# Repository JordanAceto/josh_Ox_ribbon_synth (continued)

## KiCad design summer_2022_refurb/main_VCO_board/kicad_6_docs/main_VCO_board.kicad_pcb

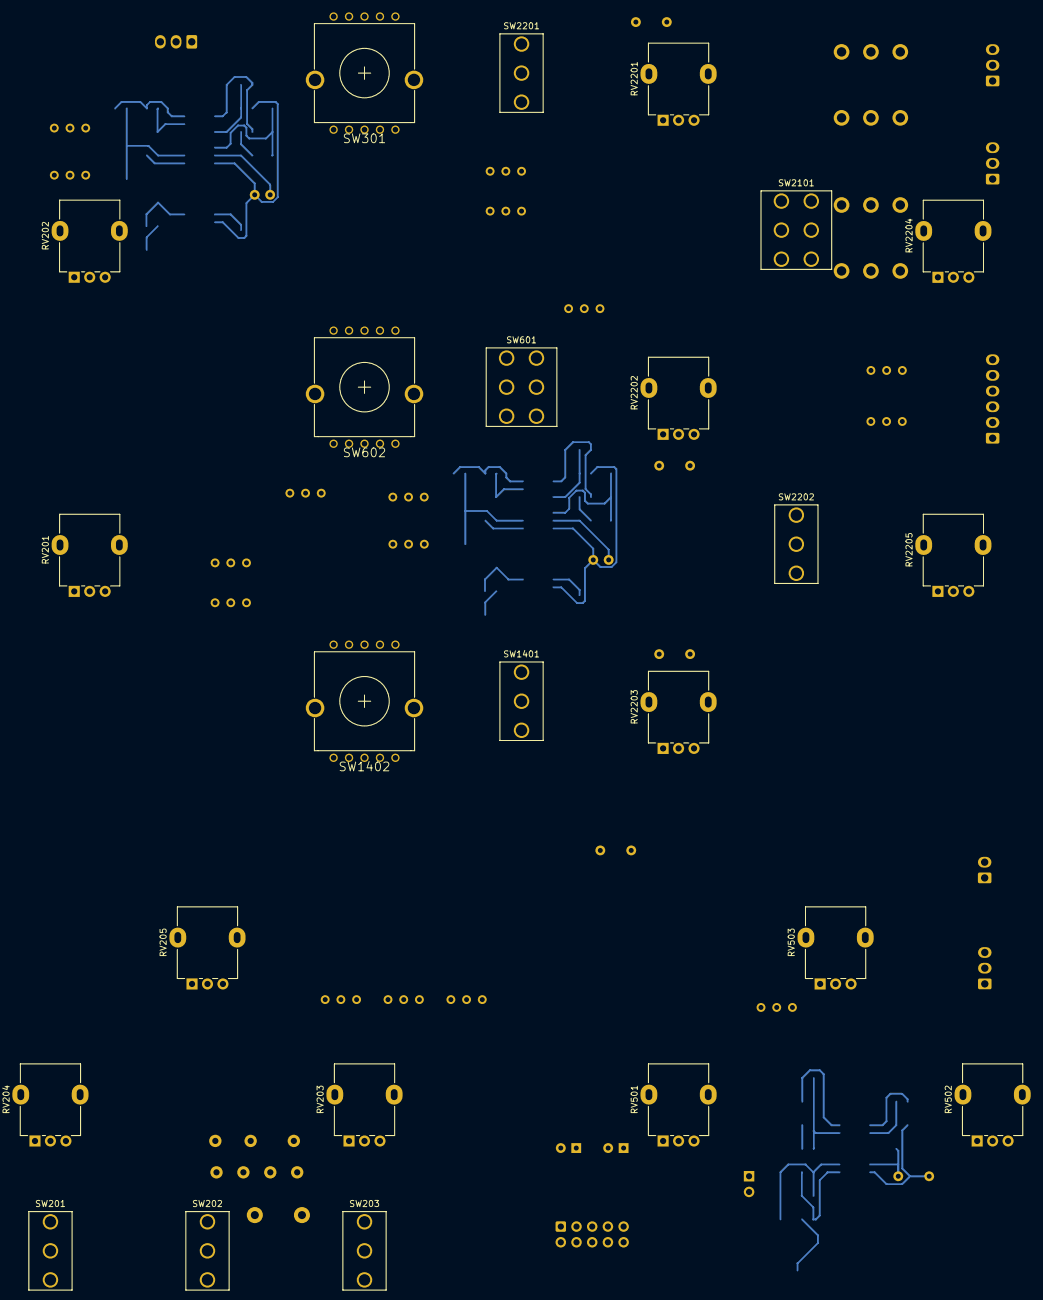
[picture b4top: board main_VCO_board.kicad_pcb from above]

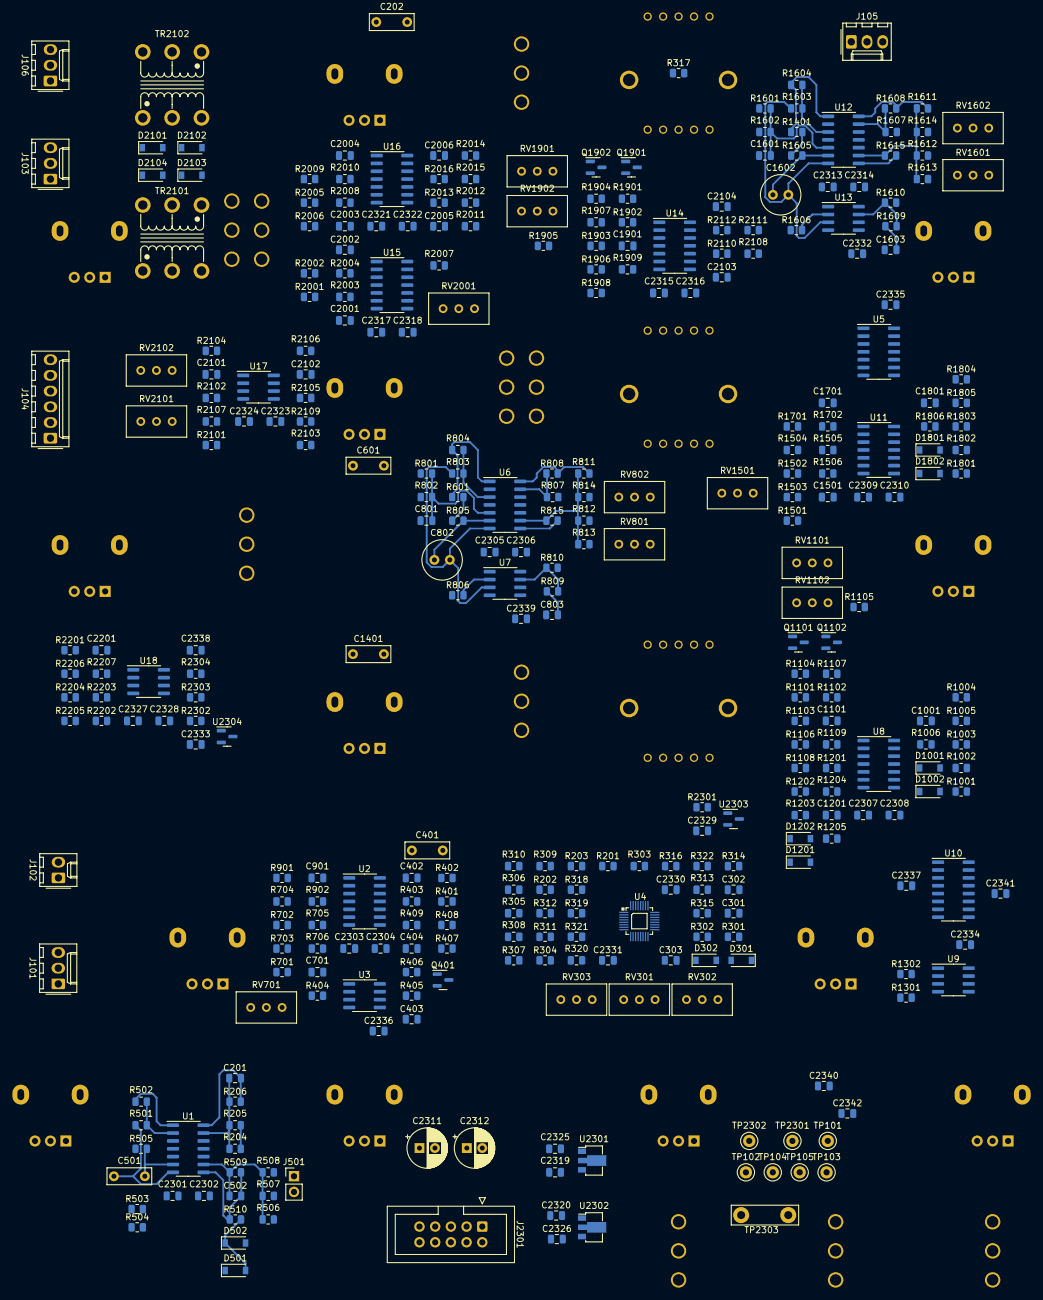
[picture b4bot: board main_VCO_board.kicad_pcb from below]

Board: 2 copper layers, 351 parts (327 on the bottom side), 214 nets.

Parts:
C201, C701, C901, C1001, C1101, C1501, C1701, C1801, C1901: C; C_0805_2012Metric
C202, C501, C601, C1401: 220n; C_Rect_L7.0mm_W2.5mm_P5.00mm
C301, C801, C1601: 10u; C_0805_2012Metric
C302: 10N; C_0805_2012Metric
C303: 3N9 COG; C_0805_2012Metric
C401: 100n; C_Rect_L7.0mm_W2.5mm_P5.00mm
C402: 20p; C_0805_2012Metric
C403, C404, C502, C803, C1603, C2003, C2004, C2101, C2102, C2103, C2104: 100p; C_0805_2012Metric
C802, C1602: 10u BP; C_Radial_D6.3mm_H5.0mm_P2.50mm
C1201, C2001, C2002, C2005, C2006, C2201: 10p; C_0805_2012Metric
C2301, C2302, C2303, C2304, C2305, C2306, C2307, C2308, C2309, C2310, C2313, C2314, C2315, C2316, C2317, C2318, C2321, C2322, C2323, C2324, C2325, C2326, C2327, C2328, C2329, C2330, C2331, C2332, C2333, C2334, C2335, C2336, C2337, C2338, C2339, C2340, C2341, C2342: 100n; C_0805_2012Metric
C2311, C2312: 10u; CP_Radial_D6.3mm_P2.50mm
C2319, C2320: 330n; C_0805_2012Metric
D301, D302, D1001, D1002, D1801, D1802: 1N4148W; D_SOD-123
D501, D502: D_Schottky; D_SOD-123
D1201, D1202: 5v1; D_SOD-123
D2101, D2102, D2103, D2104: BAT48ZFILM; D_SOD-123
J101: ribbon_port; Molex_KK-254_AE-6410-03A_1x03_P2.54mm_Vertical
J102: modosc_port; Molex_KK-254_AE-6410-02A_1x02_P2.54mm_Vertical
J103: ADSR_port; Molex_KK-254_AE-6410-03A_1x03_P2.54mm_Vertical
J104: S&H_port; Molex_KK-254_AE-6410-06A_1x06_P2.54mm_Vertical
J105: ext_con; Molex_KK-254_AE-6410-03A_1x03_P2.54mm_Vertical
J106: vcf_port; Molex_KK-254_AE-6410-03A_1x03_P2.54mm_Vertical
J501: aux_pwm; PinHeader_1x02_P2.54mm_Vertical
J2301: power_entry; IDC-Header_2x05_P2.54mm_Vertical
Q401: 2N7002; SOT-23
Q1101, Q1102, Q1901, Q1902: MMBT3904; SOT-23
R201: 150k; R_0805_2012Metric
R202: 56k; R_0805_2012Metric
R203, R804, R1004, R1006, R1604, R1804, R1806: 120k; R_0805_2012Metric
R204, R205, R311, R317, R401, R402, R403, R405, R501, R505, R509, R704, R705, R706, R805, R807, R808, R811, R813, R815, R902, R1504, R1505, R1506, R1605, R1607, R1608, R1611, R1613, R1615, R1702, R2002, R2004, R2008, R2009, R2010, R2011, R2012, R2015, R2101, R2102, R2103, R2105, R2107, R2108, R2109, R2110, R2112, R2201, R2202, R2203, R2204, R2205, R2206: 100k; R_0805_2012Metric
R206, R702, R703, R814, R1502, R1503, R1614, R2005, R2006: 200k; R_0805_2012Metric
R301, R302, R322, R406, R504, R803, R1103, R1106, R1201, R1301, R1302, R1603, R1903, R1906, R2001, R2303, R2304: 10k; R_0805_2012Metric
R303, R304, R306, R307, R308, R309, R310: 100K; R_0805_2012Metric
R305: 1m; R_0805_2012Metric
R312: 270K; R_0805_2012Metric
R313: 47K; R_0805_2012Metric
R314: 270; R_0805_2012Metric
R315: 470K; R_0805_2012Metric
R316, R2302: 4k7; R_0805_2012Metric
R318: 3K9; R_0805_2012Metric
R319, R321: 4K7; R_0805_2012Metric
R320: 12K; R_0805_2012Metric
R404, R503: 100; R_0805_2012Metric
R407, R408, R409, R2013: 20k; R_0805_2012Metric
R502: 270k; R_0805_2012Metric
R506, R2014: 220k; R_0805_2012Metric
R507, R508, R701, R812, R1501, R1612, R2016: 180k; R_0805_2012Metric
R510, R806, R810, R1606, R1610: 1k; R_0805_2012Metric
R601: 1M5; R_0805_2012Metric
R801, R1601: 8k2; R_0805_2012Metric
R802, R1602: 2k7; R_0805_2012Metric
R809, R1609: 51k; R_0805_2012Metric
R901, R1701: 33k; R_0805_2012Metric
R1001, R1002, R1005, R1801, R1802, R1805: 15k; R_0805_2012Metric
R1003, R1803: 7k5; R_0805_2012Metric
R1101, R1901: 27k; R_0805_2012Metric
R1102, R1107, R1205, R1902, R1907: 2k2; R_0805_2012Metric
R1104, R1904: 390; R_0805_2012Metric
R1105, R1905: 18k; R_0805_2012Metric
R1108, R1109, R1908, R1909: 12k; R_0805_2012Metric
R1202, R1203, R2111: R; R_0805_2012Metric
R1204, R2003: 10M; R_0805_2012Metric
R1401: 2M2; R_0805_2012Metric
R2007: 2k; R_0805_2012Metric
R2104, R2106: 330; R_0805_2012Metric
R2207: 82k; R_0805_2012Metric
R2301: 1k8; R_0805_2012Metric
RV201, RV202: 10k; Potentiometer_Alpha_RD901F-40-00D_Single_Vertical
RV203, RV204, RV205, RV501, RV502, RV503, RV2201, RV2202, RV2203, RV2204, RV2205: 100k; Potentiometer_Alpha_RD901F-40-00D_Single_Vertical
RV301, RV302, RV303, RV802, RV1602: 5k; Potentiometer_Bourns_3296W_Vertical
RV701, RV801, RV1101, RV1102, RV1501, RV1601, RV1901, RV1902, RV2001: 50k; Potentiometer_Bourns_3296W_Vertical
RV2101, RV2102: 20k; Potentiometer_Bourns_3296W_Vertical
SW201, SW202, SW203, SW1401: SW_SPDT_CO; SPDT_mini_toggle
SW301, SW602, SW1402: SR1712F-0204; SR1712F_rotary_switch
SW601, SW2101: SW_DPDT_CO; DPDT_mini_toggle
SW2201, SW2202: SW_SPDT; SPDT_mini_toggle
TP101: pwm_cv; TestPoint_Keystone_5000-5004_Miniature
TP102: oct_0; TestPoint_Keystone_5000-5004_Miniature
TP103: oct_1; TestPoint_Keystone_5000-5004_Miniature
TP104: oct_2; TestPoint_Keystone_5000-5004_Miniature
TP105: ring_mod; TestPoint_Keystone_5000-5004_Miniature
TP2301: V+; TestPoint_Keystone_5000-5004_Miniature
TP2302: V-; TestPoint_Keystone_5000-5004_Miniature
TP2303: GND; TestPoint_Bridge_Pitch7.62mm_Drill1.3mm
TR2101, TR2102: Triad_TY_141P; Triad_TY-141P
U1, U2, U6, U8, U11, U12, U14, U15, U16: TL074; SOIC-14_3.9x8.7mm_P1.27mm
U3, U7, U13: LM311; SOIC-8_3.9x4.9mm_P1.27mm
U4: SSI2130; PQN32_HandSoldering
U5: 4013; SOIC-14_3.9x8.7mm_P1.27mm
U9: LM555xM; SOIC-8_3.9x4.9mm_P1.27mm
U10: DG413xY; SOIC-16_3.9x9.9mm_P1.27mm
U17: NE5532; SOIC-8_3.9x4.9mm_P1.27mm
U18: TL072; SOIC-8_3.9x4.9mm_P1.27mm
U2301: L78L05_SOT89; SOT-89-3
U2302: L79L05_SOT89; SOT-89-3
U2303: LM4040C-2.5; SOT-23
U2304: LM4040DBZ-5; SOT-23

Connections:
+2V5 REF: C2329.1, R2301.2, U2303.1 (K)
+2V5_REF: R303.2, R320.2, R401.2, RV301.3, RV302.2, RV302.3, U4.23 (vref)
+5V: C301.2, C2325.1, C2330.1, C2332.1, C2334.1, C2335.1, C2336.1, C2339.1, C2341.1, D301.1 (K), D501.1 (K), R316.2, R317.1, R406.2, R801.1, R810.2, R1301.1, R1302.1, R1601.1, R1610.2, R2301.1, U4.27 (V+), U5.14 (VDD), U7.8 (V+), U9.8 (VCC), U10.12 (VL), U10.13 (V+), U13.8 (V+), U2301.1 (OUT)
+5V REF: C2333.1, R1004.2, R1804.2, R2302.2, R2303.2, U2304.1 (K)
+5V_REF: R203.1, R2005.1, RV201.3, RV202.3, RV503.3
+15V: C2301.1, C2303.1, C2305.1, C2307.1, C2309.1, C2311.1, C2313.1, C2315.1, C2317.1, C2319.1, C2321.1, C2323.1, C2327.1, J2301.9, J2301.10, R1103.1, R1106.1, R1903.1, R1906.1, R2302.1, TP2301.1, U1.4 (V+), U2.4 (V+), U3.8 (V+), U6.4 (V+), U8.4 (V+), U11.4 (V+), U12.4 (V+), U14.4 (V+), U15.4 (V+), U16.4 (V+), U17.8 (V+), U18.8 (V+), U2301.3 (IN)
-5V: C2326.2, C2331.2, C2337.2, C2340.2, C2342.2, D502.2 (A), U4.8 (V-), U10.4 (V-), U2302.3 (VO)
-5V REF: C2338.1, R703.1, R1503.1, R2304.1, RV802.3, RV1602.3, U18.7
-5V_REF: RV201.1, RV202.1, RV503.1
-15V: C2302.2, C2304.2, C2306.2, C2308.2, C2310.2, C2312.2, C2314.2, C2316.2, C2318.2, C2320.2, C2322.2, C2324.2, C2328.2, J2301.1, J2301.2, R1105.2, R1905.2, TP2302.1, U1.11 (V-), U2.11 (V-), U3.4 (V-), U6.11 (V-), U8.11 (V-), U11.11 (V-), U12.11 (V-), U14.11 (V-), U15.11 (V-), U16.11 (V-), U17.4 (V-), U18.4 (V-), U2302.2 (VI)
/EXT_AUDIO: J105.1, R2201.1
/MOD_OSC: J102.1, RV203.3, SW2101.1
/NOISE: J104.3, SW2202.1 (A)
/OCTAVE_0: C202.2, J104.4, J106.2, R2101.1, SW2101.3, SW2201.1 (A), TP102.1
/PWM_LFO_SQR: J101.2, R504.2
/PWM_LFO_TRI: C501.2, J104.5, R501.2, RV502.3, U1.7
/PWM_generator/PWM_CV_OUT: D501.2 (A), D502.1 (K), R201.1, R510.2, R1202.1, R2006.1, TP101.1
/audio_mixer/OUT: C2201.2, J106.1, R2207.2, U18.1
/audio_mixer/RING_MOD: RV2204.3, SW2101.5, TP105.1
/audio_mixer/SUBOSC_1: C601.2, RV2202.3, TP103.1
/audio_mixer/SUBOSC_2: C1401.2, RV2203.3, TP104.1
/main_VCO/EXT_CV: J105.2, R306.2
/main_VCO/MOD_ENV_DOWN: J103.2, SW201.3
/main_VCO/MOD_ENV_UP: J103.1, SW201.1
/main_VCO/RIBBON_CV: J101.1, R307.2
/main_VCO/S_AND_H: J104.1, SW202.1
/main_VCO/S_AND_H_MIXER: J104.2, SW202.3
/main_VCO/VCO_core/COARSE_TUNE_IN: R304.2, RV202.2
/main_VCO/VCO_core/FINE_TUNE_IN: R305.2, RV201.2
/main_VCO/VCO_core/LIN_FM_IN: C404.1, R315.2, R409.1, U2.8
/main_VCO/VCO_core/PWM_CV_IN: R201.2, R202.1, R203.2, U4.32 (pwm_in_+)
/main_VCO/VCO_core/SWITCHED_OUT: R204.1, R205.1, R322.2, U4.25 (mix_out)
/main_VCO/VCO_core/TIME_REV_IN: C403.1, Q401.1 (G), R406.1, U3.7, U4.18 (time_rev)
/main_VCO/VCO_core/V_PER_OCT_IN_3: R308.2, RV204.2
/main_VCO/VCO_core/V_PER_OCT_IN_4: R309.2, RV205.2
/main_VCO/VCO_core/V_PER_OCT_IN_5: R310.2, SW203.1
/main_VCO/lin_FM_conditioner/LIN_FM_IN: C401.2, SW203.3
/sub_osc_1/OCT_DWN_SAW: C701.2, R705.2, R706.2, SW601.3, U2.7, U10.2
/sub_osc_1/OCT_DWN_SQR: RV701.1, U5.1 (Q), U10.6
/sub_osc_1/SAW_IN: R702.1, SW601.1, U4.29 (saw_out), U10.15
/sub_osc_1/SQUARE_IN: R316.1, U4.28 (square_out), U5.3 (C), U10.10
/sub_osc_1/SQUARE_OUT: U5.11 (C), U10.7, U10.11
/sub_osc_1/STATIC_SAW_OUT: R1502.1, SW1401.1, U10.3, U10.14
/sub_osc_1/basic_pulse_shaper/PULSE_OUT: D1201.1 (K), R1205.2, SW602.5
/sub_osc_1/basic_pulse_shaper/SIGNAL_IN: C1001.2, R1006.1, R1201.1, RV1101.2, RV1101.3, SW602.3, U8.14
/sub_osc_1/level_shifter_1/IN: R815.2, R1001.2, R1005.2, U2.3 (+), U6.8
/sub_osc_1/level_shifter_1/OUT: C901.2, R902.2, SW602.4, U2.1
/sub_osc_1/passthrough_switching/SWITCH_0: R1302.2, SW601.6, U9.2 (TR)
/sub_osc_1/passthrough_switching/SWITCH_1: R1301.2, SW601.4, U9.4 (R)
/sub_osc_1/passthrough_switching/SWITCH_CTL: U9.3 (Q), U10.1, U10.8, U10.9, U10.16
/sub_osc_1/saw_animator_1/RATE_R_1: R601.1, R804.2, U6.1
/sub_osc_1/saw_animator_1/RATE_R_2: R601.2, R805.1
/sub_osc_1/saw_animator_1/SAW_IN: R806.1, R807.1, SW601.2
/sub_osc_1/tri_to_sine_shaper_1/SINE_OUT: C1101.2, R1109.2, SW602.2, U8.1
/sub_osc_2/harmonic_pulse_shaper/PULSE_OUT: C2006.2, R2016.2, SW1402.5, U16.14
/sub_osc_2/harmonic_pulse_shaper/SIGNAL_IN: C1801.2, R1806.1, R2001.1, R2002.1, RV1901.2, RV1901.3, SW1402.3, U11.14
/sub_osc_2/level_shifter_2/IN: R1615.2, R1801.2, R1805.2, U11.3 (+), U12.8
/sub_osc_2/level_shifter_2/OUT: C1701.2, R1702.2, SW1402.4, U11.1
/sub_osc_2/octave_divider_2/OCTAVE_DOWN_SAW_OUT: C1501.2, R1505.2, R1506.2, SW1401.3, U11.7
/sub_osc_2/octave_divider_2/OCTAVE_DOWN_SQR_OUT: RV1501.1, U5.13 (Q)
/sub_osc_2/saw_animator_2/RATE_R_1: R1401.1, R1604.2, U12.1
/sub_osc_2/saw_animator_2/RATE_R_2: R1401.2, R1605.1
/sub_osc_2/saw_animator_2/SAW_IN: R1606.1, R1607.1, SW1401.2
/sub_osc_2/tri_to_sine_shaper_2/SINE_OUT: C1901.2, R1909.2, SW1402.2, U14.1
GND: C302.2, C303.2, C801.2, C1601.2, C2301.2, C2302.1, C2303.2, C2304.1, C2305.2, C2306.1, C2307.2, C2308.1, C2309.2, C2310.1, C2311.2, C2312.1, C2313.2, C2314.1, C2315.2, C2316.1, C2317.2, C2318.1, C2319.2, C2320.1, C2321.2, C2322.1, C2323.2, C2324.1, C2325.2, C2326.1, C2327.2, C2328.1, C2329.2, C2330.2, C2331.1, C2332.2, C2333.2, C2334.2, C2335.2, C2336.2, C2337.1, C2339.2, C2340.1, C2341.2, C2342.1, D302.2 (A), D1202.1 (K), J101.3, J102.2, J103.3, J104.6, J105.3, J106.3, J501.2, J2301.3, J2301.4, J2301.5, J2301.6, J2301.7, J2301.8, Q401.2 (S), R202.2, R302.2, R319.1, R321.1, R322.1, R404.1, R503.2, R704.2, R802.2, R901.1, R1102.2, R1107.2, R1108.1, R1203.2, R1504.2, R1602.2, R1701.1, R1902.2, R1907.2, R1908.1, RV203.1, RV204.1, RV205.1, RV301.1, RV303.1, RV502.1, RV802.1, RV1602.1, RV2001.1, RV2201.1, RV2202.1, RV2203.1, RV2204.1, RV2205.1, SW601.5, TP2303.1, TR2101.3, TR2102.2, TR2102.6, U1.3 (+), U1.5 (+), U1.10 (+), U1.12 (+), U2.12 (+), U3.1 (GND), U4.15 (dgnd), U4.16 (agnd), U4.20 (hft_base), U5.4 (R), U5.6 (S), U5.7 (VSS), U5.8 (S), U5.10 (R), U6.10 (+), U6.12 (+), U7.1 (GND), U7.4 (V-), U8.10 (+), U8.12 (+), U9.1 (GND), U9.6 (THR), U10.5 (GND), U11.10 (+), U11.12 (+), U12.10 (+), U12.12 (+), U13.1 (GND), U13.4 (V-), U14.10 (+), U14.12 (+), U15.3 (+), U15.6 (-), U16.3 (+), U16.5 (+), U16.10 (+), U16.12 (+), U17.3 (+), U17.5 (+), U18.3 (+), U18.5 (+), U2301.2 (GND), U2302.1 (GND), U2303.2 (A), U2304.2 (A)
unnamed: C201.1, R204.2, R205.2, R206.1, U1.13 (-)
unnamed: C201.2, C202.1, R206.2, U1.14
unnamed: C301.1, R301.1
unnamed: C302.1, R314.2
unnamed: C303.1, U4.14 (tcap)
unnamed: C401.1, R402.2
unnamed: C402.1, R403.1, R407.2, R408.2, U2.14, U3.3 (-)
unnamed: C402.2, R401.1, R402.1, R403.2, U2.13 (-)
unnamed: C403.2, R405.1
unnamed: C404.2, R407.1, R409.2, U2.9 (-)
unnamed: C501.1, R505.2, U1.6 (-)
unnamed: C502.1, R506.2, R507.2, R508.2, R509.1, U1.9 (-)
unnamed: C502.2, R509.2, R510.1, U1.8
unnamed: C601.1, SW602.1
unnamed: C701.1, R701.2, R703.2, R705.1, R706.1, U2.6 (-)
unnamed: C801.1, R801.2, R802.1, U6.2 (-), U6.5 (+)
unnamed: C802.1, R805.2, U6.6 (-)
unnamed: C802.2, R803.2, R813.2, U6.7, U7.3 (-)
unnamed: C803.1, R806.2, U7.2 (+)
unnamed: C803.2, R809.1
unnamed: C1001.1, R1003.1, R1004.1, R1005.1, R1006.2, U8.13 (-)
unnamed: C1101.1, Q1101.3 (C), R1103.2, R1109.1, U8.2 (-)
unnamed: C1201.1, R1201.2, R1204.1, U8.5 (+)
unnamed: C1201.2, R1204.2, R1205.1, U8.7
unnamed: C1401.1, SW1402.1
unnamed: C1501.1, R1501.2, R1503.2, R1505.1, R1506.1, U11.6 (-)
unnamed: C1601.1, R1601.2, R1602.1, U12.2 (-), U12.5 (+)
unnamed: C1602.1, R1605.2, U12.6 (-)
unnamed: C1602.2, R1603.2, R1613.2, U12.7, U13.3 (-)
unnamed: C1603.1, R1606.2, U13.2 (+)
unnamed: C1603.2, R1609.1
unnamed: C1801.1, R1803.1, R1804.1, R1805.1, R1806.2, U11.13 (-)
unnamed: C1901.1, Q1901.3 (C), R1903.2, R1909.1, U14.2 (-)
unnamed: C2001.1, R2001.2, R2003.1, U15.5 (+)
unnamed: C2001.2, R2003.2, RV2001.3, U15.7
unnamed: C2002.1, R2002.2, R2004.1, U15.2 (-)
unnamed: C2002.2, R2004.2, R2007.1, U15.1
unnamed: C2003.1, R2005.2, R2006.2, R2008.1, U16.6 (-)
unnamed: C2003.2, R2008.2, R2009.1, U15.10 (+), U16.7
unnamed: C2004.1, R2009.2, R2010.1, U16.2 (-)
unnamed: C2004.2, R2010.2, U15.12 (+), U16.1
unnamed: C2005.1, R2011.2, R2012.2, R2013.1, U16.9 (-)
unnamed: C2005.2, R2013.2, R2015.1, U16.8
unnamed: C2006.1, R2014.2, R2015.2, R2016.1, U16.13 (-)
unnamed: C2101.1, R2101.2, R2102.1, U17.2 (-)
unnamed: C2101.2, R2104.1, U17.1
unnamed: C2102.1, R2103.2, R2105.1, U17.6 (-)
unnamed: C2102.2, R2106.1, U17.7
unnamed: C2103.1, R2108.2, R2110.1, RV2101.1, RV2102.1, U14.9 (-)
unnamed: C2103.2, R2110.2, R2111.1, U14.8
unnamed: C2104.1, R2111.2, R2112.1, RV2101.3, RV2102.3, U14.13 (-)
unnamed: C2104.2, R2112.2, SW2101.4, SW2101.6, U14.14
unnamed: C2201.1, R2201.2, R2202.2, R2203.2, R2204.2, R2205.2, R2206.2, R2207.1, U18.2 (-)
unnamed: C2338.2, R2303.1, R2304.2, U18.6 (-)
unnamed: D301.2 (A), D302.1 (K), R301.2, R302.1, U4.17 (hard_sync)
unnamed: D1001.1 (K), R1001.1, R1002.2, U8.9 (-)
unnamed: D1001.2 (A), D1002.1 (K), U8.8
unnamed: D1002.2 (A), R1002.1, R1003.2
unnamed: D1201.2 (A), D1202.2 (A)
unnamed: D1801.1 (K), R1801.1, R1802.2, U11.9 (-)
unnamed: D1801.2 (A), D1802.1 (K), U11.8
unnamed: D1802.2 (A), R1802.1, R1803.2
unnamed: D2101.1 (K), D2103.2 (A), TR2101.4
unnamed: D2101.2 (A), D2102.1 (K), TR2102.3
unnamed: D2102.2 (A), D2104.1 (K), TR2101.6
unnamed: D2103.1 (K), D2104.2 (A), TR2102.1
unnamed: J501.1, R508.1
unnamed: Q401.3 (D), R408.1, U2.10 (+)
unnamed: Q1101.1 (B), R1101.2, R1102.1
unnamed: Q1101.2 (E), R1104.1, RV1102.3
unnamed: Q1102.1 (B), R1107.1
unnamed: Q1102.2 (E), R1104.2, RV1102.1
unnamed: Q1102.3 (C), R1106.2, R1108.2, U8.3 (+)
unnamed: Q1901.1 (B), R1901.2, R1902.1
unnamed: Q1901.2 (E), R1904.1, RV1902.3
unnamed: Q1902.1 (B), R1907.1
unnamed: Q1902.2 (E), R1904.2, RV1902.1
unnamed: Q1902.3 (C), R1906.2, R1908.2, U14.3 (+)
unnamed: R303.1, R304.1, R305.1, R306.1, R307.1, R308.1, R309.1, R310.1, R311.1, R312.2, U4.7 (expo_freq)
unnamed: R311.2, RV301.2
unnamed: R312.1, RV303.2
unnamed: R313.1, RV302.1
unnamed: R313.2, U4.22 (expo_scale)
unnamed: R314.1, U4.26 (bw_comp)
unnamed: R315.1, U4.21 (lin_freq)
unnamed: R317.2, SW301.1
unnamed: R318.1, R319.2, U4.2 (sine_in_+)
unnamed: R318.2, U4.1 (tri_out), U4.31 (pwm_in_-)
unnamed: R320.1, R321.2, U4.3 (sine_in_-)
unnamed: R404.2, R405.2, U3.2 (+)
unnamed: R501.1, R502.1, U1.2 (-)
unnamed: R502.2, R504.1, RV501.3, U1.1
unnamed: R503.1, RV501.1
unnamed: R505.1, RV501.2
unnamed: R506.1, RV502.2
unnamed: R507.1, RV503.2
unnamed: R701.1, RV701.2, RV701.3
unnamed: R702.2, R704.1, U2.5 (+)
unnamed: R803.1, R804.1, U6.3 (+)
unnamed: R807.2, R808.1, U6.13 (-)
unnamed: R808.2, R811.1, U6.14
unnamed: R809.2, R810.1, RV801.1, U7.7
unnamed: R811.2, R812.2, R813.1, R814.2, R815.1, U6.9 (-)
unnamed: R812.1, RV801.2, RV801.3
unnamed: R814.1, RV802.2
unnamed: C901.1, R901.2, R902.1, U2.2 (-)
unnamed: R1101.1, RV1101.1
unnamed: R1105.1, RV1102.2
unnamed: R1202.2, R1203.1, U8.6 (-)
unnamed: R1501.1, RV1501.2, RV1501.3
unnamed: R1502.2, R1504.1, U11.5 (+)
unnamed: R1603.1, R1604.1, U12.3 (+)
unnamed: R1607.2, R1608.1, U12.13 (-)
unnamed: R1608.2, R1611.1, U12.14
unnamed: R1609.2, R1610.1, RV1601.1, U13.7
unnamed: R1611.2, R1612.2, R1613.1, R1614.2, R1615.1, U12.9 (-)
unnamed: R1612.1, RV1601.2, RV1601.3
unnamed: R1614.1, RV1602.2
unnamed: C1701.1, R1701.2, R1702.1, U11.2 (-)
unnamed: R1901.1, RV1901.1
unnamed: R1905.1, RV1902.2
unnamed: R2007.2, U15.9 (-), U15.13 (-)
unnamed: R2011.1, U15.8
unnamed: R2012.1, U15.14
unnamed: R2014.1, RV2001.2
unnamed: R2102.2, R2104.2, R2107.1, TR2101.1
unnamed: R2103.1, SW2101.2
unnamed: R2105.2, R2106.2, R2109.1, TR2101.5
unnamed: R2107.2, RV2101.2
unnamed: R2108.1, TR2102.4
unnamed: R2109.2, RV2102.2
unnamed: R2202.1, RV2201.2
unnamed: R2203.1, RV2202.2
unnamed: R2204.1, RV2203.2
unnamed: R2205.1, RV2204.2
unnamed: R2206.1, RV2205.2
unnamed: RV203.2, SW203.2
unnamed: RV204.3, SW201.2
unnamed: RV205.3, SW202.2
unnamed: RV303.3, U4.6 (hf_track)
unnamed: RV2201.3, SW2201.2 (B)
unnamed: RV2205.3, SW2202.2 (B)
unnamed: SW301.2, U4.13 (aux_2_mix)
unnamed: SW301.3, U4.9 (tri_mix)
unnamed: SW301.4, U4.10 (saw_mix)
unnamed: SW301.5, U4.11 (pulse_mix)
unnamed: U4.5 (aux_in_2), U4.24 (sine_out)
unnamed: U5.2 (~Q), U5.5 (D)
unnamed: U5.9 (D), U5.12 (~Q)

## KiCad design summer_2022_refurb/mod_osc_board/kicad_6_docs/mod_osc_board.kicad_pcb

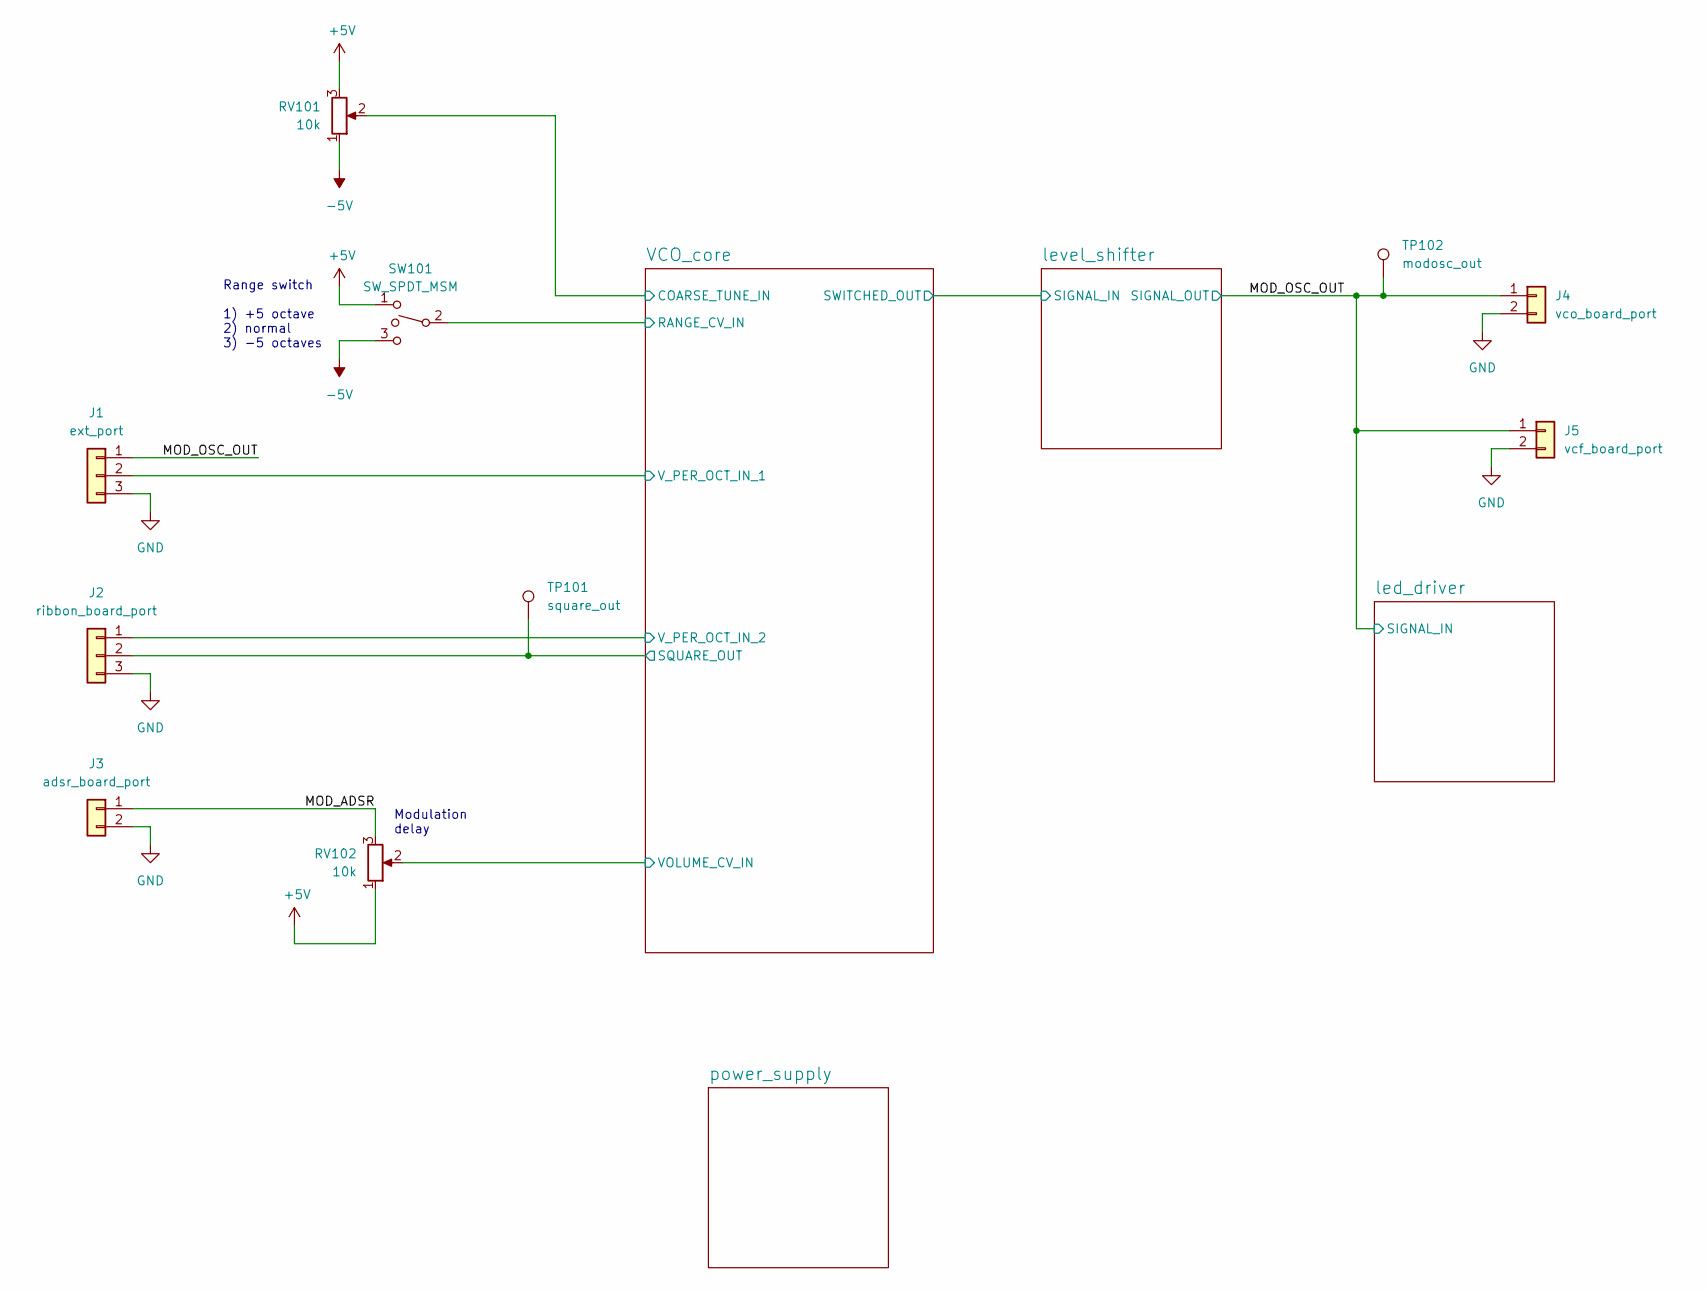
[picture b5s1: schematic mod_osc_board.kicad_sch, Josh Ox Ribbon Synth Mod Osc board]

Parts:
J1: ext_port; Molex_KK-254_AE-6410-03A_1x03_P2.54mm_Vertical
J2: ribbon_board_port; Molex_KK-254_AE-6410-03A_1x03_P2.54mm_Vertical
J3: adsr_board_port; Molex_KK-254_AE-6410-02A_1x02_P2.54mm_Vertical
J4: vco_board_port; Molex_KK-254_AE-6410-02A_1x02_P2.54mm_Vertical
J5: vcf_board_port; Molex_KK-254_AE-6410-02A_1x02_P2.54mm_Vertical
RV101, RV102: 10k; Potentiometer_P260T
SW101: SW_SPDT_MSM; SPDT_mini_toggle
TP101: square_out; TestPoint_Keystone_5000-5004_Miniature
TP102: modosc_out; TestPoint_Keystone_5000-5004_Miniature

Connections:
+5V: RV101.3, RV102.1, SW101.1; also elsewhere on the board
-5V: RV101.1, SW101.3; also elsewhere on the board
/MOD_ADSR: J3.1, RV102.3
/MOD_OSC_OUT: J1.1, J4.1, J5.1, TP102.1; also elsewhere on the board
/VCO_core/COARSE_TUNE_IN: RV101.2; also elsewhere on the board
/VCO_core/RANGE_CV_IN: SW101.2; also elsewhere on the board
/VCO_core/SQUARE_OUT: J2.2, TP101.1; also elsewhere on the board
/VCO_core/VOLUME_CV_IN: RV102.2; also elsewhere on the board
/VCO_core/V_PER_OCT_IN_1: J1.2; also elsewhere on the board
/VCO_core/V_PER_OCT_IN_2: J2.1; also elsewhere on the board

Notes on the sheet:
Range switch 1) +5 octave 2) normal 3) -5 octaves
Modulation delay

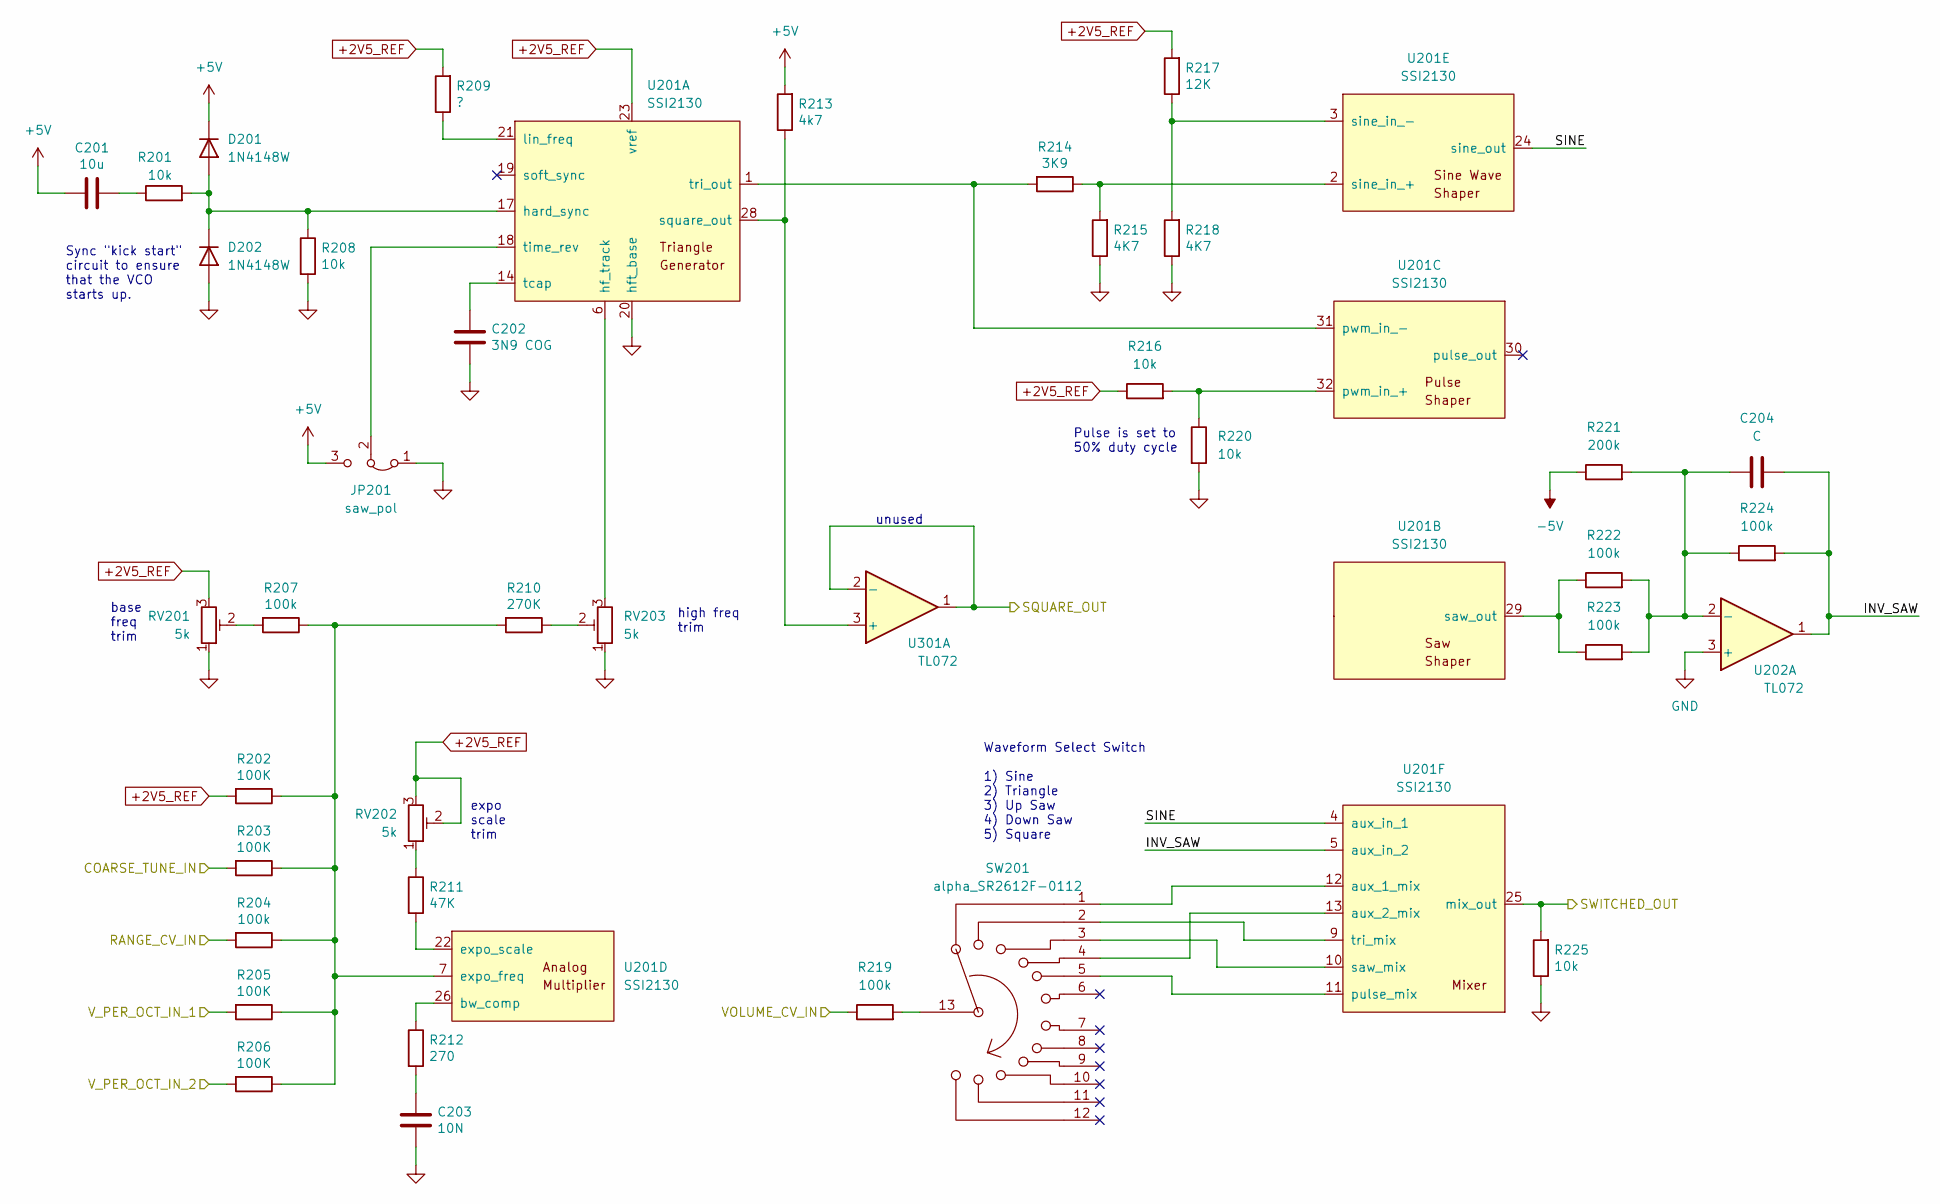
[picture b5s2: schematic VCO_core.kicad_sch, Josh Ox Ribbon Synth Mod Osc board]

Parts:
C201: 10u; C_0805_2012Metric
C202: 3N9 COG; C_0805_2012Metric
C203: 10N; C_0805_2012Metric
C204: C; C_0805_2012Metric
D201, D202: 1N4148W; D_SOD-123
JP201: saw_pol; SolderJumper-3_P1.3mm_Bridged12_RoundedPad1.0x1.5mm
R201, R208, R216, R220, R225: 10k; R_0805_2012Metric
R202, R203, R205, R206: 100K; R_0805_2012Metric
R204, R207, R219, R222, R223, R224: 100k; R_0805_2012Metric
R209: ?; R_0805_2012Metric
R210: 270K; R_0805_2012Metric
R211: 47K; R_0805_2012Metric
R212: 270; R_0805_2012Metric
R213: 4k7; R_0805_2012Metric
R214: 3K9; R_0805_2012Metric
R215, R218: 4K7; R_0805_2012Metric
R217: 12K; R_0805_2012Metric
R221: 200k; R_0805_2012Metric
RV201, RV202, RV203: 5k; Potentiometer_Bourns_3296W_Vertical
SW201: alpha_SR2612F-0112; apha_SR2612F-0112
U201: SSI2130; PQN32_HandSoldering
U202, U301: TL072; SO-8_5.3x6.2mm_P1.27mm

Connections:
+2V5_REF: R202.2, R209.2, R216.1, R217.2, RV201.3, RV202.2, RV202.3, U201.23 (vref); also elsewhere on the board
+5V: C201.2, D201.1 (K), JP201.3 (B), R213.2; also elsewhere on the board
-5V: R221.1; also elsewhere on the board
/VCO_core/COARSE_TUNE_IN: R203.2; also elsewhere on the board
/VCO_core/INV_SAW: C204.2, R224.2, U201.5 (aux_in_2), U202.1
/VCO_core/RANGE_CV_IN: R204.2; also elsewhere on the board
/VCO_core/SINE: U201.4 (aux_in_1), U201.24 (sine_out)
/VCO_core/SQUARE_OUT: U301.1, U301.2 (-); also elsewhere on the board
/VCO_core/SWITCHED_OUT: R225.2, U201.25 (mix_out); also elsewhere on the board
/VCO_core/VOLUME_CV_IN: R219.1; also elsewhere on the board
/VCO_core/V_PER_OCT_IN_1: R205.2; also elsewhere on the board
/VCO_core/V_PER_OCT_IN_2: R206.2; also elsewhere on the board
unnamed: C201.1, R201.1
unnamed: C202.1, U201.14 (tcap)
unnamed: C203.1, R212.2
unnamed: C204.1, R221.2, R222.2, R223.2, R224.1, U202.2 (-)
unnamed: JP201.2 (C), U201.18 (time_rev)
unnamed: R202.1, R203.1, R204.1, R205.1, R206.1, R207.1, R210.2, U201.7 (expo_freq)
unnamed: R207.2, RV201.2
unnamed: D201.2 (A), D202.1 (K), R201.2, R208.1, U201.17 (hard_sync)
unnamed: R209.1, U201.21 (lin_freq)
unnamed: R210.1, RV203.2
unnamed: R211.1, RV202.1
unnamed: R211.2, U201.22 (expo_scale)
unnamed: R212.1, U201.26 (bw_comp)
unnamed: R213.1, U201.28 (square_out), U301.3 (+)
unnamed: R214.1, R215.2, U201.2 (sine_in_+)
unnamed: R214.2, U201.1 (tri_out), U201.31 (pwm_in_-)
unnamed: R216.2, R220.1, U201.32 (pwm_in_+)
unnamed: R217.1, R218.2, U201.3 (sine_in_-)
unnamed: R219.2, SW201.13
unnamed: R222.1, R223.1, U201.29 (saw_out)
unnamed: RV203.3, U201.6 (hf_track)
unnamed: SW201.1, U201.12 (aux_1_mix)
unnamed: SW201.2, U201.9 (tri_mix)
unnamed: SW201.3, U201.10 (saw_mix)
unnamed: SW201.4, U201.13 (aux_2_mix)
unnamed: SW201.5, U201.11 (pulse_mix)

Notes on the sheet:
Waveform Select Switch 1) Sine 2) Triangle 3) Up Saw 4) Down Saw 5) Square
high freq trim
unused
Pulse is set to 50% duty cycle
expo scale trim
Sync "kick start" circuit to ensure that the VCO starts up.
base freq trim

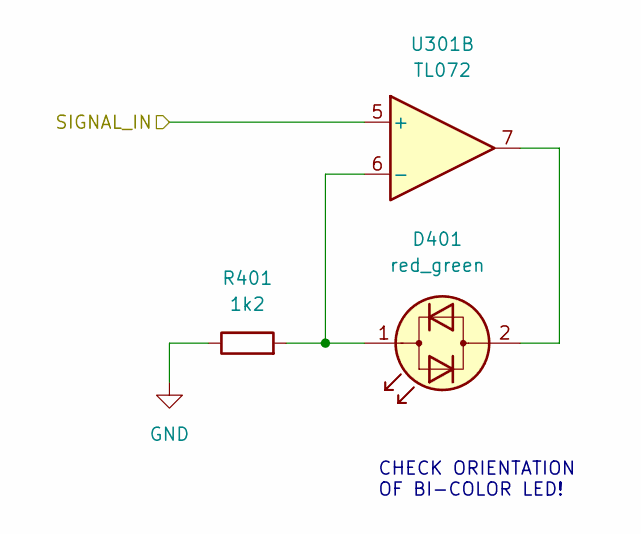
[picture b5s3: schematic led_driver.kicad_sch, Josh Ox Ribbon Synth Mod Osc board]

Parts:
D401: red_green; LED_D5.0mm
R401: 1k2; R_0805_2012Metric
U301: TL072; SO-8_5.3x6.2mm_P1.27mm

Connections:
/MOD_OSC_OUT: U301.5 (+); also elsewhere on the board
unnamed 21: D401.1 (KA), R401.2, U301.6 (-); also elsewhere on the board
unnamed 22: D401.2 (AK), U301.7; also elsewhere on the board

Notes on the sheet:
CHECK ORIENTATION OF BI-COLOR LED!

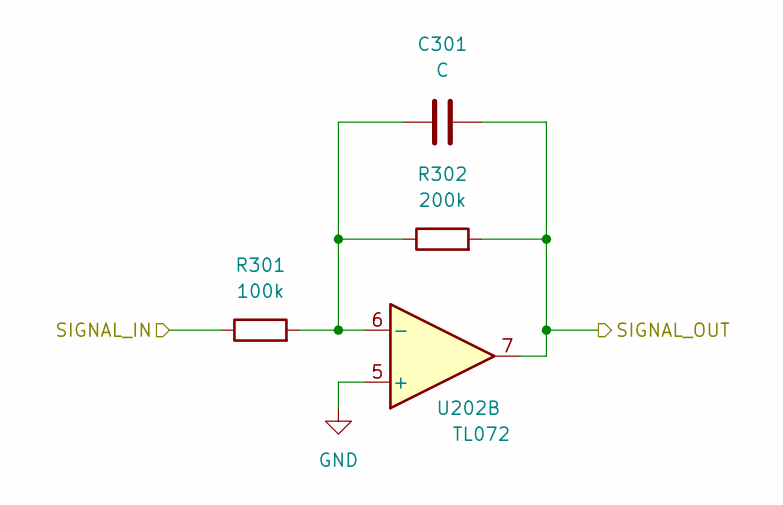
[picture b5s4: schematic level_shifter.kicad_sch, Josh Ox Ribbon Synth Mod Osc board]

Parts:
C301: C; C_0805_2012Metric
R301: 100k; R_0805_2012Metric
R302: 200k; R_0805_2012Metric
U202: TL072; SO-8_5.3x6.2mm_P1.27mm

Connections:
/MOD_OSC_OUT: C301.2, R302.2, U202.7; also elsewhere on the board
/VCO_core/SWITCHED_OUT: R301.1; also elsewhere on the board
unnamed: C301.1, R301.2, R302.1, U202.6 (-)
